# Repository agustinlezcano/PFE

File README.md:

<h1 style="text-align: center;"> Proyecto Final de Estudios </h1>

<h2 style="text-align: center;"> Ingeniería en Mecatrónica </h2>

<h2 style="text-align: center;"> Facultad de Ingeniería - Universidad Nacional de Cuyo </h2>

<h1 style="text-align: center;"> Robot paralelo pick-and-place para la preparación de pedidos </h1>

<h3 style="text-align: center;">Ing. Eric Sanchez </h3>
<h3 style="text-align: center;">Autores: Aguero Emanuel, Lezcano Agustin </h3>
<h3 style="text-align: center;">Mendoza, Argentina </h3>
<h3 style="text-align: center;">2026 </h3>

El proyecto desarrollado consiste en el diseno e implementación de un sistema robótico paralelo para operativa pick-and-place, cuyo objetivo principal es trasladar objetos desde un punto inicial (A) hasta un punto final (B) a partir de su deteccion mediante técnicas de visióon artificial. El sistema esta orientado a manipular objetos que arriban desde lo que se simula ser una cinta transportadora, identificarlos dentro del espacio de trabajo y posicionarlos de manera precisa en un contenedor correspondiente a un pedido, simulando un flujo típico de procesos logísticos modernos.

Para esto, se realizo la modificación estructural y funcional de un robot modelo MK2, reemplazando sus servomotores originales por motores Paso a Paso en todas sus articulaciones, con el fin de mejorar la precision de posicionamiento y el control del movimiento. El efector final incorpora un electroiman que permite la sujeción de piezas metálicas durante el ciclo operativo.  

El desarrollo abarca múltiples areas: la modificación estructural hacia motores Paso a Paso; el calculo de la cinemática directa e inversa del manipulador; la integración y calibración de los motores; y la planificacion de trayectorias que permitan un movimiento suave, eficiente y seguro del robot. Asimismo, se integra un sistema de visión artificial basado en algoritmos de inferencia para 
la deteccion y localización de objetos en el entorno. 

Finalmente, se implementa una arquitectura de comunicacion mediante ROS2, por medio de la cual se establecen nodos dedicados a la interaccion entre la computadora encargada del procesamiento de vision y el envío de consignas de posición, y el microcontrolador STM32 responsable del control de los motores. Esta infraestructura permite el intercambio confiable de informacion entre los distintos módulos del sistema y constituye la base para la coordinación del proceso completo de manipulación robótica.

---

## Imágenes

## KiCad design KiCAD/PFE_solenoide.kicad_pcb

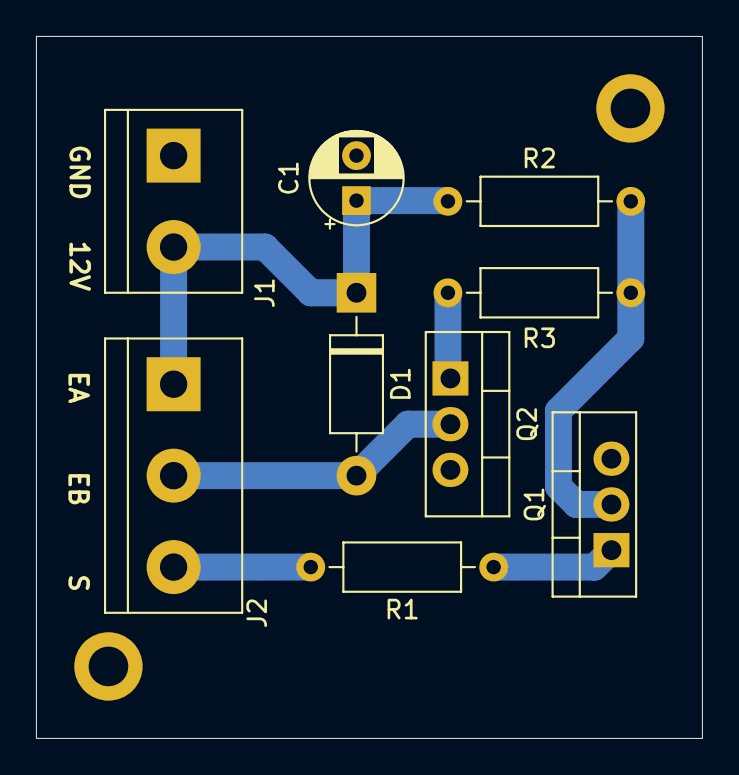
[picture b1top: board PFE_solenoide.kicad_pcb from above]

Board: 2 copper layers, 37.0 x 39.0 mm, 11 parts (0 on the bottom side), 7 nets.

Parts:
C1: C; CP_Radial_D5.0mm_P2.50mm
D1: 1N4001; D_DO-41_SOD81_P10.16mm_Horizontal
H1, H2: MountingHole_2.2mm_M2_ISO14580_Pad
J1: Vin; TerminalBlock_bornier-2_P5.08mm
J2: E+uC; TerminalBlock_bornier-3_P5.08mm
Q1: NPN; TO-220-3_Vertical
Q2: NMOS; TO-220-3_Vertical
R1: 10k; R_Axial_DIN0207_L6.3mm_D2.5mm_P10.16mm_Horizontal
R2: 47k; R_Axial_DIN0207_L6.3mm_D2.5mm_P10.16mm_Horizontal
R3: 330; R_Axial_DIN0207_L6.3mm_D2.5mm_P10.16mm_Horizontal

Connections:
GND: C1.2, H1.1, H2.2, J1.1, Q1.3 (E), Q2.3 (S)
unnamed: D1.2 (A), J2.2, Q2.2 (G)
unnamed: C1.1, D1.1 (K), J1.2, J2.1, R2.1
unnamed: J2.3, R1.2
unnamed: Q1.1 (C), R1.1
unnamed: Q1.2 (B), R2.2, R3.1
unnamed: Q2.1 (D), R3.2

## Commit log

2023-07-12 Commit inicial
2023-07-25 Diseño 3D SolidEdge
2023-07-25 caracteristicas robot
2023-07-28 Robot completo formato step
2023-07-28 Robot en formado STEP
2023-07-29 Ensamble corregido, eslabones centrados
2023-08-06 reverse changes
2023-08-06 Cinematica modificada
2024-10-30 Estructura inicial
2024-12-31 versiones de prueba
2025-01-23 deleted unused files
2025-01-28 refactor kinematics algorithms
2025-02-17 updated img/gui/kinematics
2025-02-22 added joint angles validation
2025-04-21 Trajectory Planning
2025-04-30 (#20) fix LSPB generation
2025-06-16 (#21) fix utils & communication modules
2025-07-17 #22 mv ros files
2025-08-01 Valida angulos corregido, cinv corroborada y ecuaciones theta angulo micro
2025-08-30 Correccion dimensiones robot y verificacion de tool en la c_inv
2025-08-30 Piezas 3D actualizadas a Robot con PaP
2025-10-26 (#24) update STM32 & ROS modules
2025-10-26 Nuevos soportes, robot primitivo y modificacion engranajes motores
2025-11-01 [update] delete mx utils duplicated folder
2025-11-02 MicroROS con control de motores por PWM
2025-11-04 Robot con PaP en Solid
2025-11-11 [update] main modified-segregation
2025-11-11 [update] main.h modified
2025-11-12 Carpeta informe PDF guardar ahi + img + latex
2025-11-12 Pequeños cambios 3D
2025-11-13 [update] refactor code
2025-11-21 [update] change project structure
    microcontroller changes
2025-12-01 Modelo de YOLOv11
2025-12-01 Matlab, plano Z=0 para encontrar interseccion con el piso
2025-12-01 Ajuste en ficha220, se creo un pie para camara y stl de engranaje motor
2025-12-08 [update] cambios en ROS (Python)
2025-12-08 [update] cambios en STM micro-ROS
2025-12-08 Calculo del espacio de trabajo teorico y real + cambios minimos en 3D
2025-12-08 [update] agregado setup y ws_micro_ros
2025-12-08 [update] add Python UI publishers
2025-12-08 Implementacion de motores en codigo de freeRTOS
2026-02-09 Initial plan
2026-02-09 Initial plan for fixing errors in orchestrator_project
2026-02-09 Fix critical errors in publisher.py and related files
2026-02-09 Address code review comments - improve documentation and error handling
2026-02-16 [update] add socket client for Vision & UI changes
2026-02-19 add publisher and node ui
2026-02-19 [update] add new classes for UI & trajectory planning
2026-02-21 Add multipoiny Trajectory
2026-02-22 Trajectory planner con estado de trayectoria por puntos
2026-02-23 update Trama
2026-02-23 fix Trama
2026-02-23 add electromagnet
2026-02-24 publisher con point y traj_planner con traj_state
2026-02-24 update traj trama
2026-02-24 add electromagnet management
2026-02-24 refacrot Trama
2026-02-24 fix doCmd calls
2026-02-25 update homing wait
2026-02-25 fix type doCmd
2026-02-25 update YOLO files
2026-02-25 traj with fixed dt
2026-02-26 Add files via upload
    upload latex img
2026-02-26 upload latex files
2026-02-26 pdf informe
2026-03-01 [update] tests codes
2026-03-02 Create KiCAD folder
2026-03-02 Added KiCAD files
2026-03-02 Mover archivos a carpeta KiCAD
2026-03-02 Enhance README with project description and images
    Updated README to include project details and images.
2026-03-02 Modify images to display at 50% width
    Adjusted image display size in README.
2026-03-02 Modify image size for Escudo_uncuyo.jpg
    Updated image size for Escudo_uncuyo.jpg in README
2026-03-03 Server return nearest object
2026-03-04 update ui and publisher
2026-03-04 fix publisher type
2026-03-04 ikine desde ui
2026-03-05 ikine con Trama usando publisher cmd
2026-03-06 move to next object if not detected in vision
2026-03-08 added tests and datasheets
2026-03-08 folder named MATLAB
2026-03-08 last stm32 code full working all
2026-03-08 Update .gitignore without python cache
2026-03-10 orden archivos 3D
2026-03-10 renombre carpeta 3D
2026-04-01 Add images section to README
    Added images section with various robot-related images.
2026-04-01 Add images for ROS2
    Added images for ROS2 nodes and graphical interface.
